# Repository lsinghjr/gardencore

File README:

Gardencore
====================

All in one garden monitoring system using the spark core.

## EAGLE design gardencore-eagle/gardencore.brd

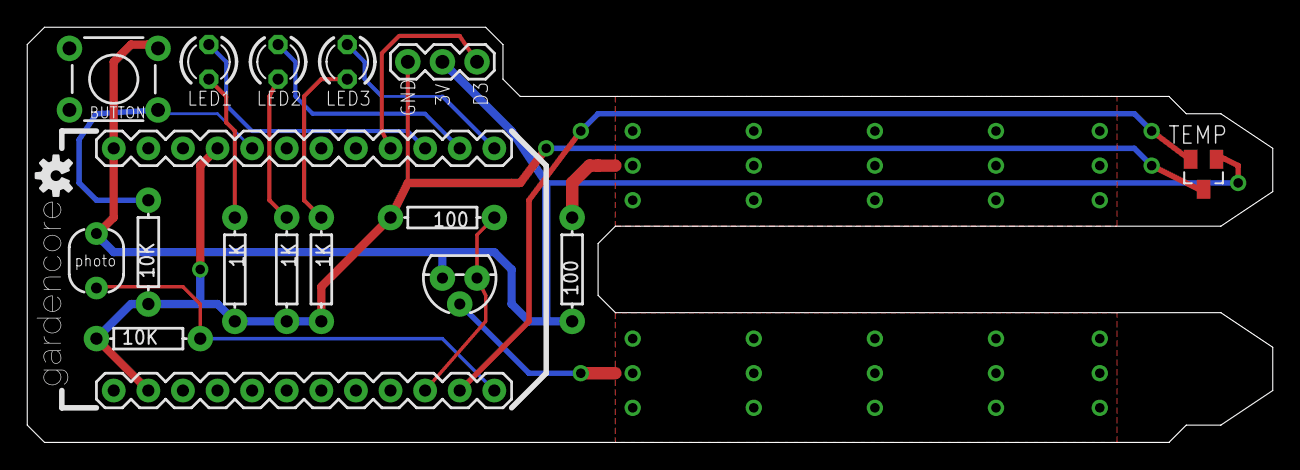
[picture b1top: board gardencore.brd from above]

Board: 2 copper layers, 91.4 x 30.5 mm, 18 parts (0 on the bottom side), 13 nets.

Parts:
BUTTON: TACTILE-PTH
JP1, JP2: M12PTH; 1X12-SMALL-PADS
JP3: 1X03
LED1: green; LED3MM
LED2: blue; LED3MM
LED3: yellow; LED3MM
NPN: NPN; TO-92
R1: PHOTOCELLPTH; PHOTOCELL
R2, R8: 10K; AXIAL-0.3
R3, R7: 100; AXIAL-0.3
R4, R5, R6: 1K; AXIAL-0.3
TEMP: LM50; SOT23
U$1: OSHW-LOGO-S

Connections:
+3V3: BUTTON.3, JP2.1, JP3.2, NPN.3, R1.2, R3.P$1, TEMP.1
A0: JP1.12, R1.1, R2.P$2
A1: JP1.11, TEMP.2
D0: JP2.12, LED3.A
D1: JP2.11, LED2.A
D2: JP2.10, LED1.A
D3: JP2.9, JP3.3
D7: BUTTON.1, JP2.5, R8.P$2
GND: JP1.2, JP2.4, JP3.1, R2.P$1, R4.P$2, R5.P$2, R6.P$2, R7.P$2, R8.P$1, TEMP.3
unnamed: LED3.K, R6.P$1
unnamed: LED2.K, R5.P$1
unnamed: LED1.K, R4.P$1
unnamed: JP1.10, NPN.1, R7.P$1

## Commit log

2013-08-13 first files
2013-08-13 readme
2013-08-13 added switch, changed size of board
2013-08-13 Fixed airwires
2013-08-13 Design rule fixes
2013-08-13 Added gerbers
2013-08-14 logo labels and design rule check
2013-08-15 External digital pin, added part labels to silkscreen
2013-08-21 bill of materials

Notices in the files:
parts and their libraries:
SparkFun-Passives: Licensing: CC v3.0 Share-Alike You are welcome to use this library for commercial purposes.
